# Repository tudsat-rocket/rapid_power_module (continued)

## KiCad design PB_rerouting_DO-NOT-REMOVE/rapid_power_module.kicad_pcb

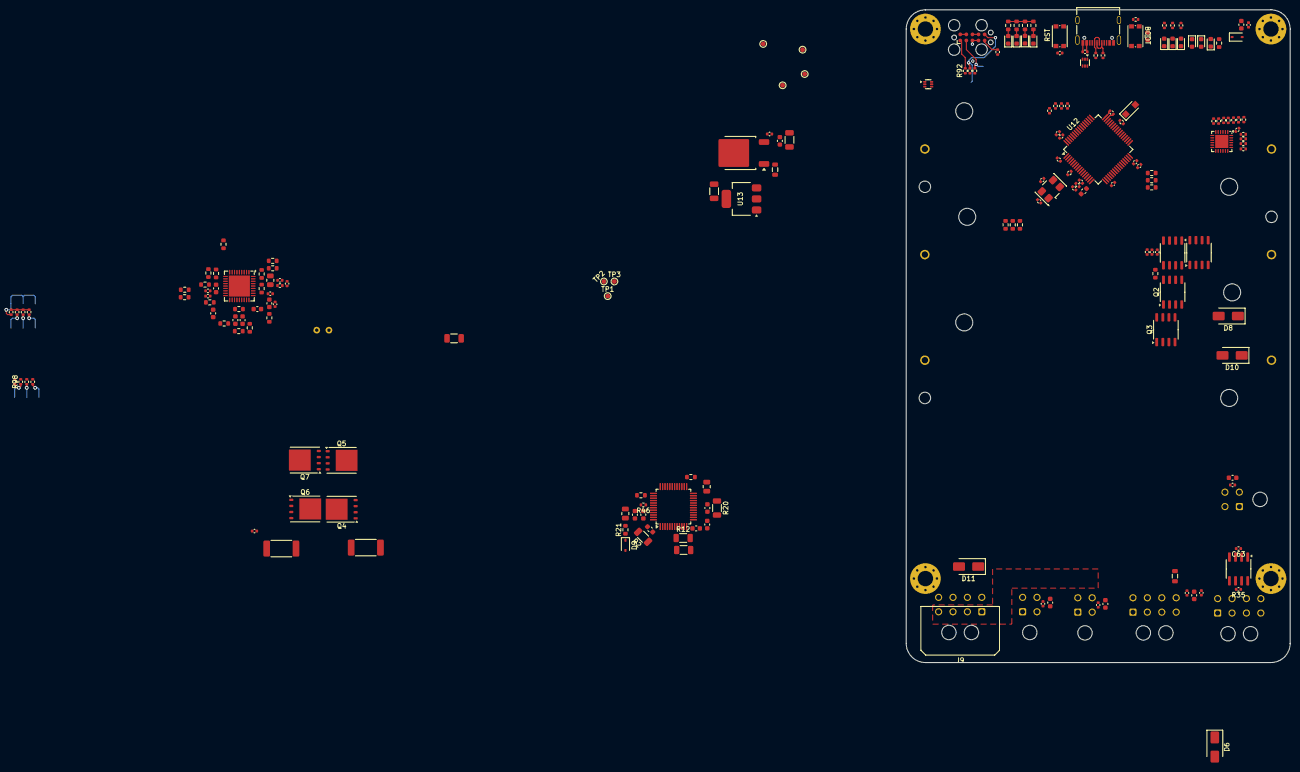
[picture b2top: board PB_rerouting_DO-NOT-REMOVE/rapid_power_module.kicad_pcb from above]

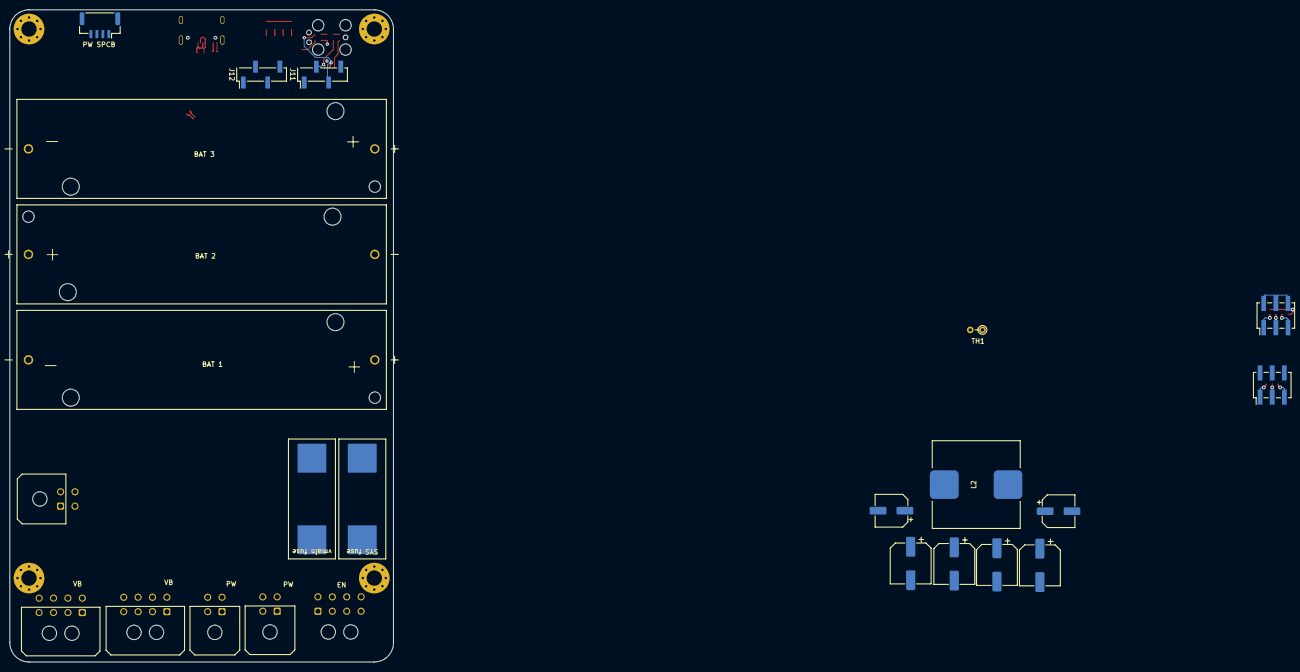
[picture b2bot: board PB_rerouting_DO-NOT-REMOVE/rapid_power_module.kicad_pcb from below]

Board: 4 copper layers, 80.0 x 136.0 mm, 210 parts (23 on the bottom side), 131 nets.

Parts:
BT1, BT2, BT3: Battery_Cell; BAT_1043
C1, C3, C37, C38, C44, C45, C60, C63, C68, C69, C70, C71, C72, C79, C81: 100n; C_0402_1005Metric
C2, C4, C5, C6: 82u; CP_Elec_8x6.9
C7, C8: 10u; CP_Elec_6.3x5.9
C9, C10, C20, C65, C74, C75: 1u; C_0402_1005Metric
C11: 1u; R_0402_1005Metric
C12, C13: 100n; R_0402_1005Metric
C14, C15, C16, C17: 220n; C_0603_1608Metric
C18, C39, C43, C47, C48, C58: 470n; C_0603_1608Metric
C19: 1u; C_0805_2012Metric
C21: 2u2; C_0805_2012Metric
C23: 3u3; C_0402_1005Metric
C24: 100p; C_0603_1608Metric
C46, C49: 47n; C_0603_1608Metric
C61: 10u; C_1206_3216Metric
C62: 0.47uF; C_1206_3216Metric
C67: 4u7; C_0402_1005Metric
C73, C76, C83, C85, C87, C89, C91: 10n; C_0402_1005Metric
C77, C78: 10p; C_0402_1005Metric
C80: 22u; C_1206_3216Metric
C82, C84, C86, C88, C90: 10u; C_0603_1608Metric
D4, D9: D_SOD-323
D5, D7, D16, D19, D21, D23: green; LED_0603_1608Metric
D6, D8, D10, D11: D_SMA
D17, D22: red; LED_0603_1608Metric
D18, D20: yellow; LED_0603_1608Metric
D24: Vz = 3.6V; Nexperia_CFP3_SOD-123W
F1: 5A; Fuseholder_Cylinder-5x20mm_Wuerth_696103101002-SMD_Horizont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
F3: 20A; Fuseholder_Cylinder-5x20mm_Wuerth_696103101002-SMD_Horizont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
FB1: 120R; L_0603_1608Metric
FB2, FB3: 120R; L_0805_2012Metric
H1, H2, H3, H4: MountingHole_Pad; MountingHole_3.2mm_M3_Pad_Via
J1, J3, J9: Conn_02x04_Top_Bottom; Molex_Micro-Fit_3.0_43045-0800_2x04_P3.00mm_Horizontal
J2, J4: Conn_02x03_Odd_Even; PinHeader_2x03_P2.54mm_Vertical_SMD
J6, J7, J8: Molex MicroFit 2x2; Molex_Micro-Fit_3.0_43045-0400_2x02_P3.00mm_Horizontal
J10: JST-GH 4Pin; JST_GH_SM04B-GHS-TB_1x04-1MP_P1.25mm_Horizontal
J11, J12: SWD Header; PinHeader_1x04_P2.54mm_Vertical_SMD_Pin1Left
J16: USB_C_Receptacle_USB2.0; USB_C_Receptacle_Palconn_UTC16-G
J17: TC2050; Tag-Connect_TC2050-IDC-FP_2x05_P1.27mm_Vertical
L2: 5u6; Wuerth 7443557560
Q1, Q2, Q3, Q12: AOSP21321; SO-8_3.9x4.9mm_P1.27mm
Q4: HiDRV1; TDSON-8-1
Q5: LoDRV1; TDSON-8-1
Q6: HiDRV2; TDSON-8-1
Q7: LoDRV2; TDSON-8-1
R1: 2.4; R_0402_1005Metric
R2, R11, R12, R20: 20; R_1206_3216Metric
R3: 15k; R_0603_1608Metric
R4, R13, R46, R95: 10k; R_0402_1005Metric
R5, R9, R26, R74, R89, R90: 1k; R_0402_1005Metric
R6, R7, R10, R18, R19, R96: 5k1; R_0402_1005Metric
R8, R30: 49k9; R_0603_1608Metric
R14, R15, R16, R17, R34: 1k; R_0603_1608Metric
R21: 100; R_0603_1608Metric
R22: 10R; R_0603_1608Metric
R23, R32: 4k7; R_0603_1608Metric
R24: 100k; R_0603_1608Metric
R25, R94, R97: 20k; R_0402_1005Metric
R27: 50k; R_0402_1005Metric
R28: 20k; R_0603_1608Metric
R29: 680; R_0603_1608Metric
R31: 50k; R_0603_1608Metric
R33: 300k; R_0603_1608Metric
R35: 120; C_0402_1005Metric
R36: 200k; R_0603_1608Metric
R37, R41, R79, R80: 10; R_0603_1608Metric
R38, R65: 5m; R_2512_6332Metric_Pad1.40x3.35mm_HandSolder
R39: 4.7k; R_0603_1608Metric
R40, R42, R64, R69, R70, R72, R91: 10k; R_0603_1608Metric
R43: 68k; R_0603_1608Metric
R44: 1000k; R_0805_2012Metric
R45: 4k7; R_0402_1005Metric
R66, R67: 4.7k; R_0402_1005Metric
R73, R75, R77, R78: 22R; R_0402_1005Metric
R76: 100k; R_0402_1005Metric
R82: 22k; R_0603_1608Metric
R83: 49k9; R_0402_1005Metric
R86, R87, R88, R92: 22; R_0402_1005Metric
R98: 15k; R_0402_1005Metric
SW1, SW2: KMR721NGLFS; SW_Push_1P1T_NO_CK_KMR2
TH1: Thermistor_NTC; R_Axial_DIN0204_L3.6mm_D1.6mm_P2.54mm_Vertical
TP1: BuckBoostOut; TestPoint_Pad_D1.0mm
TP2: TP_CAN_TX; TestPoint_Pad_D1.0mm
TP3: TP_CAN_RX; TestPoint_Pad_D1.0mm
TP4: TP_USB_D+; TestPoint_Pad_D1.0mm
TP5: TP_USB_D-; TestPoint_Pad_D1.0mm
TP6: TP_USB_CC2; TestPoint_Pad_D1.0mm
TP7: TP_USB_CC1; TestPoint_Pad_D1.0mm
U1: BQ25756RRVR; Texas_RHH0036C_VQFN-36-1EP_6x6mm_P0.5mm_EP4.4x4.4mm
U2: CYPD3177-24LQ; QFN-24-1EP_4x4mm_P0.5mm_EP2.75x2.75mm
U3: BQ76952PFBR; TQFP-48_7x7mm_P0.5mm
U10: L7805; TO-252-2
U11: MCP2562-E-SN; SOIC-8_3.9x4.9mm_P1.27mm
U12: STM32F105RCTx; LQFP-64_10x10mm_P0.5mm
U13: AZ1117I-3.3; SOT-223-3_TabPin2
U14, U15: TPD4E1U06; SOT-563
Y3: 8MHz 12pF; Crystal_SMD_5032-4Pin_5.0x3.2mm

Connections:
3.3V PD: C11.1, C12.1, C13.1, R6.1, R10.1, R18.1, U2.23 (VDDD)
+3V3: C67.1, C68.1, C69.1, C70.1, C71.1, C72.1, C75.1, C76.1, C80.2, FB1.1, J11.1, J12.1, J17.7, J17.8, R14.1, R15.1, R16.1, R17.1, R26.1, R34.1, R39.1, R40.1, R42.1, R64.1, R66.2, R67.2, R69.1, R70.1, R72.1, R89.1, R90.1, U11.5 (Vio), U12.1 (VBAT), U12.19 (VDD), U12.32 (VDD), U12.48 (VDD), U12.64 (VDD), U13.2 (VO), U15.5 (IO4)
+3VA3: C73.1, C74.1, FB1.2, U12.13 (VDDA)
+5V: C60.1, C61.2, C63.2, J17.9, J17.10, U10.3 (OUT), U11.3 (VDD), U13.3 (VI), U15.6 (V_{cc})
+VSW: C84.1, C85.1, C86.1, C87.1, C88.1, C89.1, D11.2 (A), J6.3, J6.4, J7.3, J7.4, J8.3, J8.4, J9.1, J9.2, J9.3, J9.4
/D0+: J16.A6 (D+), J16.B6 (D+), R75.2, U14.5 (IO4)
/D0-: J16.A7 (D-), J16.B7 (D-), R73.1, U14.4 (IO3)
/J1-SWCLK: J11.3, J17.6, R88.1, U15.4 (IO3)
/J1-SWDIO: J11.2, J17.2, R86.2, U15.1 (IO1)
/J1-SWO: J17.5, R87.2, U15.2 (IO2)
/VBUS: C9.1, C23.2, J16.A4 (VBUS), J16.A9 (VBUS), J16.B4 (VBUS), J16.B9 (VBUS), Q2.5 (D), Q2.6 (D), Q2.7 (D), Q2.8 (D), Q12.5 (D), Q12.6 (D), Q12.7 (D), Q12.8 (D), R4.1, R8.1, R45.2, U2.18 (VBUS_IN), U14.6 (V_{cc})
/VCC_BQ76952: C18.2, C19.2, C24.2, R21.2, U3.47 (BAT)
/V_in_post_sense: C4.1, C7.1, Q4.5 (D), R65.2, R79.1
ACN: C38.1, C39.1, R79.2, U1.29 (ACN)
ACOV: R33.2, R43.1, U1.35 (ACOV)
ACP: C37.2, C39.2, R80.2, U1.30 (ACP)
ACUV: R33.1, R44.2, U1.34 (ACUV)
BAL_ALERT: R23.1, U3.25 (ALERT), U12.24 (PC4)
BOOT: R76.2, SW1.1 (A), U12.60 (BOOT0), U14.1 (IO1)
BTST1: C49.2, U1.26 (BTST1)
BTST2: C46.2, U1.20 (BTST2)
BuckBoostOut: C6.1, Q6.5 (D), R38.1, R41.2, TP1.1
CAN+: J1.7, J3.7, R35.1, U11.7 (CANH)
CAN-: J1.3, J3.3, R35.2, U11.6 (CANL)
CAN_2_H: J1.8, J3.8
CAN_2_L: J1.4, J3.4
CAN_RX: TP3.1, U11.4 (RXD), U12.61 (PB8)
CAN_TX: TP2.1, U11.1 (TXD), U12.62 (PB9)
CC1: J16.A5 (CC1), TP7.1, U2.15 (CC1)
CC2: J16.B5 (CC2), TP6.1, U2.14 (CC2)
CE: R91.2, U1.7 (CE), U12.40 (PC9)
CELL 0: C17.2, R20.2, U3.16 (VC0)
CELL 1: C15.2, C16.1, R12.2, U3.15 (VC1)
CELL 2: C14.2, C15.1, R11.2, U3.1 (VC15), U3.2 (VC14), U3.3 (VC13), U3.4 (VC12), U3.5 (VC11), U3.6 (VC10), U3.7 (VC9), U3.8 (VC8), U3.9 (VC7), U3.10 (VC6), U3.11 (VC5), U3.12 (VC4), U3.13 (VC3), U3.14 (VC2)
CELL 3: C14.1, R2.2, U3.48 (VC16)
CHRG_IND_LED_1: D5.1 (K), U12.54 (PD2)
CHRG_IND_LED_2: D7.1 (K), U12.55 (PB3)
CHRG_IND_LED_3: D16.1 (K), U12.56 (PB4)
CHRG_IND_LED_4: D23.1 (K), U12.57 (PB5)
FAULT: R40.2, U2.9 (FAULT), U12.27 (PB1)
FLIP: R39.2, U2.10 (FLIP), U12.26 (PB0)
GND: BT3.N (-), C1.2, C2.2, C3.2, C4.2, C5.2, C6.2, C7.2, C8.2, C11.2, C12.2, C13.2, C16.2, C17.1, C19.1, C20.2, C21.1, C23.1, C24.1, C37.1, C38.2, C44.2, C45.1, C47.2, C48.2, C58.1, C60.2, C61.1, C62.2, C63.1, C65.2, C67.2, C68.2, C69.2, C70.2, C71.2, C72.2, C73.2, C74.2, C75.2, C76.2, C77.2, C78.2, C79.1, C80.1, C81.2, C82.2, C83.2, C84.2, C85.2, C86.2, C87.2, C88.2, C89.2, C90.2, C91.2, D20.1 (K), D21.1 (K), D24.2 (A), H1.1, H2.1, H3.1, H4.1, J1.1, J1.2, J3.1, J3.2, J6.1, J6.2, J7.1, J7.2, J8.1, J8.2, J10.3, J10.4, J11.4, J12.4, J16.A1 (GND), J16.A12 (GND), J16.B1 (GND), J16.B12 (GND), J16.S1 (SHIELD), J17.3, J17.4, Q5.1 (S), Q5.2 (S), Q5.3 (S), Q7.1 (S), Q7.2 (S), Q7.3 (S), R7.2, R13.2, R19.2, R20.1, R23.2, R24.2, R25.2, R27.2, R29.2, R31.2, R43.2, R76.1, R83.2, R91.1, R94.2, R95.2, R96.2, R97.2, R98.2, SW2.1 (A), TH1.2, U1.17 (PGND), U1.22 (PGND), U1.37 (EPAD), U2.6 (ISNK_FINE), U2.19 (GND), U2.22 (GND), U2.25 (GND), U3.17 (VSS), U3.18 (SRP), U3.20 (SRN), U3.36 (REGIN), U3.37 (BREG), U3.41 (LD), U10.2 (GND), U11.2 (VSS), U11.8 (STBY), U12.12 (VSSA), U12.18 (VSS), U12.31 (VSS), U12.47 (VSS), U12.63 (VSS), U13.1 (GND), U14.3 (GND), U15.3 (GND), Y3.2, Y3.4
GPIO_1: R42.2, U2.8 (GPIO_1), U12.28 (PB2)
HIDRV1: Q4.4 (G), U1.27 (HIDRV1)
HIDRV2: Q6.4 (G), U1.19 (HIDRV2)
HSE_IN: C78.1, U12.5 (PD0), Y3.3
HSE_OUT: R74.1, U12.6 (PD1)
I2C_SCL: R67.1, R78.1, U1.1 (SCL), U2.13 (HPI_SCL), U3.26 (SCL), U12.58 (PB6)
I2C_SDA: R66.1, R77.1, U1.2 (SDA), U2.12 (HPI_SDA), U3.27 (SDA), U12.59 (PB7)
INT: R72.2, U1.3 (INT), U12.51 (PC10)
ISNK_COARSE: R10.2, R13.1, U2.5 (ISNK_COARSE)
LODRV1: Q5.4 (G), U1.25 (LODRV1)
LODRV2: Q7.4 (G), U1.21 (LODRV2)
NRST: C79.2, R92.1, SW2.2 (B), U12.7 (NRST), U14.2 (IO2)
unnamed: BT1.N (-), BT2.P (+), R11.1
unnamed: BT2.N (-), BT3.P (+), R12.1
unnamed: C1.1, R1.1
unnamed: C77.1, R74.2, Y3.1
unnamed: D4.1 (K), J10.1, J10.2
unnamed: D5.2 (A), R14.2
unnamed: D7.2 (A), R15.2
unnamed: D9.1 (K), R21.1
unnamed: D11.1 (K), F1.1
unnamed: D16.2 (A), R16.2
unnamed: D17.2 (A), R26.2
unnamed: D18.2 (A), R89.2
unnamed: D19.2 (A), R90.2
unnamed: D22.2 (A), R69.2
unnamed: D23.2 (A), R17.2
unnamed: F1.2, FB2.2
unnamed: J2.1, R25.1
unnamed: J2.2, J2.4, J2.6, R94.1, U1.10 (ILIM_HIZ)
unnamed: J2.3, R95.1
unnamed: J2.5, R96.1
unnamed: J4.1, R27.1
unnamed: J4.2, J4.4, J4.6, R83.1, U1.9 (ICHG)
unnamed: J4.3, R97.1
unnamed: J4.5, R98.1
unnamed: F3.1, J9.5, J9.6, J9.7, J9.8
unnamed: J12.2, R78.2
unnamed: J12.3, R77.2
unnamed: J17.1, R92.2
unnamed: Q1.5 (D), Q1.6 (D), Q1.7 (D), Q1.8 (D), Q12.1 (S), Q12.2 (S), Q12.3 (S)
unnamed: C9.2, C10.2, Q1.4 (G), Q12.4 (G), R4.2, R5.1
unnamed: Q2.4 (G), Q3.4 (G), R8.2, R9.1
unnamed: Q2.1 (S), Q2.2 (S), Q2.3 (S), Q3.5 (D), Q3.6 (D), Q3.7 (D), Q3.8 (D)
unnamed: R3.2, R28.1
unnamed: R29.1, R82.2
unnamed: R30.2, R36.1
unnamed: R34.2, SW1.2 (B)
unnamed: C48.1, R22.2, U1.23 (DRV_SUP)
unnamed: R28.2, R30.1, U1.12 (FB)
unnamed: R3.1, U1.11 (FBG)
unnamed: R31.1, U1.36 (FSW_SYNC)
unnamed: R32.1, R82.1, TH1.1, U1.8 (TS)
unnamed: C20.1, U2.24 (VCCD)
unnamed: C18.1, U3.46 (CP1)
unnamed: R24.1, U3.38 (FUSE)
unnamed: R46.1, U3.42 (PACK)
unnamed: C21.2, U3.24 (REG18)
unnamed: C58.2, FB3.1, U10.1 (IN)
PACK+: BT1.P (+), C3.1, C5.1, C8.1, C90.1, C91.1, D4.2 (A), D9.2 (A), F3.2, FB3.2, R2.1, R36.2, R37.2, R38.2, R46.2
PG: D22.1 (K), U1.6 (PG), U12.36 (PB15)
REGN: C47.1, R22.1, R32.2, U1.24 (REGN)
RST_SHUT: U3.33 (RST_SHUT), U12.2 (PC13)
SAFE_PWR_EN: R9.2, U2.4 (SAFE_PWR_EN)
SAFE_PWR_OUT: D10.2 (A), Q3.1 (S), Q3.2 (S), Q3.3 (S)
SRN: C43.2, C45.2, R37.1, U1.13 (SRN)
SRP: C43.1, C44.1, R41.1, U1.14 (SRP)
STAT1: D20.2 (A), R64.2, U1.4 (STAT1), U12.38 (PC7)
STAT2: D21.2 (A), R70.2, U1.5 (STAT2), U12.37 (PC6)
STAT_LED0: D17.1 (K), U12.33 (PB12)
STAT_LED1: D18.1 (K), U12.34 (PB13)
STAT_LED2: D19.1 (K), U12.35 (PB14)
SW1: C49.1, L2.1, Q4.1 (S), Q4.2 (S), Q4.3 (S), Q5.5 (D), U1.28 (SW1)
SW2: C46.1, L2.2, Q6.1 (S), Q6.2 (S), Q6.3 (S), Q7.5 (D), U1.18 (SW2)
SWCLK: R88.2, U12.49 (PA14)
SWDIO: R86.1, U12.46 (PA13)
SWO: R87.1, U12.50 (PA15)
TS2: U3.22 (TS2), U12.17 (PA3)
USB_D+: R75.1, TP4.1, U12.45 (PA12)
USB_D-: R73.2, TP5.1, U12.44 (PA11)
USB_FS_VBUS: D24.1 (K), R45.1, U12.42 (PA9)
USB_PD_INTERRUPT: U2.7 (~HPI_INT), U12.21 (PA5)
USB_PD_OUT: C10.1, D8.2 (A), Q1.1 (S), Q1.2 (S), Q1.3 (S), U2.11 (VDC_OUT)
VBUS_FET_EN: R5.2, U2.3 (VBUS_FET_EN)
VBUS_MAX: R6.2, R7.1, U2.2 (VBUS_MAX)
VBUS_MIN: R18.2, R19.1, U2.1 (VBUS_MIN)
V_in: C2.1, C62.1, C65.1, D6.1 (K), D8.1 (K), D10.1 (K), R1.2, R44.1, R65.1, R80.1, U1.32 (VAC), U1.33 (VAC)
charging_voltage: D6.2 (A), J1.5, J3.5
main_voltage: C81.1, C82.1, C83.1, FB2.1, J1.6, J3.6

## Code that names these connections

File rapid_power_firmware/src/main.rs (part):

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    let p = embassy_stm32::init(config);
    defmt::info!("main.rs: Embassy is up.");

    // ---- BQ25756 CE pin (PC9) ----
    // Drive LOW to allow charging (CE is active-low on this design)
    let bq_ce = Output::new(p.PC9, Level::Low, Speed::VeryHigh);
    // keep it in scope (or move into a StaticCell) so it stays driven for the lifetime
    core::mem::forget(bq_ce);

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    let usb_driver: OtgDriver<'static, USB_OTG_FS> = OtgDriver::new_fs(
        p.USB_OTG_FS,
        Irqs,
        p.PA12,
        p.PA11,
        EP_MEMORY.init([0; 4096]),
        otg_cfg,
    );
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    // I2C bus + shared device handles
    let mut i2c_cfg = I2cConfig::default();
    i2c_cfg.frequency = Hertz(100_000);
    let raw_i2c = I2c::new(p.I2C1, p.PB6, p.PB7, Irqs, p.DMA1_CH6, p.DMA1_CH7, i2c_cfg);
    let bus_mutex: &'static I2cBusMutex = I2C_BUS.init(Mutex::new(raw_i2c));

    // BQ25756
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        let bq25756 = bq25756::Bq25756::new(i2c_dev);
        let bq25756_mutex = BQ25756_DRV.init(Mutex::new(bq25756));

        let bq_int   = ExtiInput::new(p.PC10, p.EXTI10, Pull::Up);
        let bq_stat1 = ExtiInput::new(p.PC7,  p.EXTI7,  Pull::Up);
        let bq_stat2 = ExtiInput::new(p.PC6,  p.EXTI6,  Pull::Up);
        let bq_pg    = ExtiInput::new(p.PB15, p.EXTI15, Pull::Up);

        defmt::info!("main.rs: Spawning BQ25756 tasks");
        spawner
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    // --- BQ76952 FIRST ---
    #[cfg(feature = "bq76952")]
    {
        let ts2 = Flex::new(p.PA3);
        let i2c_dev: I2cDev<'static> = I2cDevice::new(bus_mutex);
        let bq = bq76952::Bq76952::new(i2c_dev, 0x08, 5);
        let bq_mutex = BQ76952_DRV.init(Mutex::new(bq));
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                let cypd_mutex = CYPD_DRV.init(Mutex::new(cypd_tmp));

                // IRQ pin
                let hpi_int = ExtiInput::new(p.PA5, p.EXTI5, Pull::Up);

                // Spawn tasks ONLY if probe passed
                spawner.spawn(cypd3177::device::cypd_monitor_task(cypd_mutex)).unwrap();
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    // CAN
    #[cfg(feature = "can")]
    {
        let can = can::init(p.CAN1, p.PB8, p.PB9, Irqs);
        spawner.spawn(can::run(can)).unwrap();
    }
} // <-- CLOSES main
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
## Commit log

2024-11-18 add readme
2024-11-18 fix image path
2025-03-22 Added 2 ICs to library, added these ICs to the schaltplan. Added Readme Notes
2025-04-23 Weitere Änderungen, aber noch nicht fertig
2025-04-28 Zwischenstand
2025-04-29 Cell Balancer Reading Circuit cleaned up
2025-04-29 Cleaned up
2025-05-05 Added MCU and connected relevant Pins
2025-05-10 clean up
2025-05-10 more cleanup
2025-05-11 project cleanup and renaming
2025-05-11 update parts
2025-05-11 Added Falstadt simulator file, incomplete
2025-05-12 added some connectors, components and todos
2025-05-12 excel
2025-05-19 Added BG25756 and exchanged it against BG25750 Changed the circuitry accordingly ToDo: Change values of resistors and caps to match final voltage and capacity
2025-05-20 Werte geupdatet
2025-05-20 finalized excel sheet -> picture & values in scematic not adjusted jet, added some footprints and parts
2025-05-21 Added comments
2025-05-23 changed values in the Buck Boost Section according to the excel sheet
2025-05-26 Added first design for the usb PD funtionality and added comments
2025-05-26 Kommentare
2025-05-31 added drawio overview in docs
2025-06-07 Added TODOs in Schematic
2025-06-08 added diode logic
2025-06-13 added charge indicator LEDs
2025-06-13 fixed vbus sense for usb pd
2025-06-13 balancer circuit with new chip
2025-06-13 changed GND in the PACK
2025-06-15 comments and a bit of cleanup
2025-06-23 changed back to bq76952
2025-06-23 saving work
2025-06-23 changed GND to VSS
2025-06-23 changed buck boost values according to the excel tool
2025-06-23 work on the Balancer
2025-06-23 added balancer datasheet
2025-06-27 added some footprints
2025-07-04 some comments and checking
2025-07-04 added most footprints
2025-07-07 Removed BJT as it is not required when not using REG1 and REG2
2025-07-21 Added Testpoints and some LCSC numbers
2025-07-28 Routing for 4 pin connectors
2025-08-01 rough component placement
2025-08-01 some placement changes
2025-08-02 more routing work
2025-08-02 Added Footprints for MOSFETs
2025-08-02 Further Routing work and fixed the Q Pins
2025-08-03 Placed the NMOS near Inductor, moved STM out of the way and fixed the Battery Pins
2025-08-03 Fixed wuerth cap footprints and values
2025-08-03 Added footprints and LCSC
2025-08-04 Added Diode and new connector type
2025-08-04 fix diode and more routing work
2025-08-04 Added Pin connections from USB PD to STM, removed non essential resistors
2025-08-06 more routing
2025-08-06 Fixed Balancer Pins so that LDO is not used and LDO input is grounded
2025-08-06 Annotated change
2025-08-07 improve area shapes
2025-08-07 check DRC and fix issues
2025-08-11 gnd changes in scematic and routing, tbc
2025-08-11 some changes in the scematic
2025-08-11 assimilated ground connections
2025-08-12 croschecking scematic, some changes there and new routing approach
2025-08-14 scematic adaptations and routing
2025-08-15 Stop tracking embedded repo rapid_power_fw, added LD schemtaic
2025-08-15 Ignore rapid_power_fw
2025-08-15 some scematic changes and routing
2025-08-16 Added new Resistor for LD so that it can detect load and charger
2025-08-17 Continue with routing, esp. signal traces for mcu
2025-08-17 Length matching, some cleanup, additional via placement
2025-08-17 finish routing and silkscreen improvements
2025-08-17 Finishing touches (Zone optimizations to reduce antenna effect, wider battery connection zones)
2025-08-17 Replace wrong battery manager footprint
2025-08-21 Fix: remove embedded repo and commit project updates
2025-08-29 Add basic running embassy loop
2025-09-01 Update dependencies and add CYPD3177 driver
    - Updated `defmt`, `defmt-rtt`, and `panic-probe` dependencies to version 1.0.1, 1.0.0, and 1.0.0 respectively.
    - Upgraded `embassy-stm32`, `embassy-executor`, `embassy-time`, `embassy-embedded-hal`, and `embassy-sync` to their latest versions.
    - Got it to actually run.
    - Introduced a new module `cypd3177.rs` for the CYPD3177 USB-PD async driver, implementing HPI over I²C.
    - Refactored `main.rs` to integrate the new CYPD3177 driver, including tasks for USB communication and monitoring the CYPD3177 status.
    - Added support for handling USB CDC communication and periodic monitoring of the CYPD3177 device status.
2025-09-02 Add async driver for BQ76952 battery monitor
    - Implemented the Bq76952 struct with methods for initialization, reading measurements, and configuring settings.
    - Added support for direct commands and subcommands as per the Technical Reference Manual (TRM).
    - Created register addresses and bit masks in a separate `regs` module.
    - Defined necessary types, enums, and error handling in the `types` module.
    - Included methods for voltage, current, temperature readings, and protection settings.
    - Added functionality for I2C address configuration and data memory writing.
2025-09-04 Enhance BQ76952 driver with TS2 control and wake functionality; add new features for GPIO handling in main application
2025-09-04 Add BQ25756 driver with async support and integrate into main application
2025-09-08 Added initial working driver for v3 of power module
2025-09-09 temp commit
2025-09-24 Cleaned up BQ25756, cleaned up repo
2025-09-24 Refactor BQ25756 configuration and enhance driver functionality
    - Updated default features in Cargo.toml
    - Added known errors section in README.md
    - Introduced new helper functions and improved existing methods in device.rs for better handling of DPM limits
    - Enhanced logging for charge and input current limits
    - Adjusted logging period and maximum charge/input current in config.rs
2025-09-27 Comments and Thermistor Code
2025-09-27 BQ25756: Fixed bit shift handling in ICHG and Voltage DPM
2025-09-27 Fixed max battery voltage
2025-10-13 fix broken trace
2025-11-04 Added new charger architecture of rapid_power_module.kicad_sch
2025-11-04 fixed open-message
2025-11-04 added todos
2025-11-05 added hierarchical pins for submodules
2025-11-09 added second i2c bus; cleaned up sub-schematic-structure
2025-11-10 Cleaned up, added some Balancer designs
2025-11-10 Cleaned up, added some Balancer designs, cleaned up folder
2025-11-22 cleaned up hierarchical structure; changed connectors
2025-11-30 added SA balancer design (WiP)
2025-12-03 added balancer thermistor info; changed MCU pinout to support CAN bootloading
2025-12-07 Changed Balancer layout to support OVP, UVP and UVP-circumvention; added UVP-circumvention arming connector
2025-12-14 added explanations for balancer schematic and some component values
2025-12-15 changed balancer layout according to new requirements (i.e. removed OVP/UVP, OTP/UTP, OCP/UCP); reduced arming connectors to only one
2025-12-21 added info text
2025-12-22 finalized new balancer layout (removed R_SNS and implemented the resulting consequences); removed charger shipping mode
2026-01-13 changed arming_pin2battery connection
2026-01-28 implemented changes according to errors found in the schematic design review (wip)
2026-02-02 added missing footprints and validated all lcsc numbers; started pcb-layouting
2026-03-09 started routing Please enter the commit message for your changes. Lines starting
2026-03-16 still working on routing
2026-03-22 completed signal routing
2026-04-11 almost finished routing
2026-04-19 finished pcb routing. needs feedback
2026-04-21 implemented improvements based on feedback; Voltage/Current sensing still missing
2026-04-21 added 3D model for 20A fuse holder
2026-04-23 adding voltage and current sensing capabilities. WIP
2026-04-27 calculated sensing-resistor values
2026-04-29 added current sensing circuit
2026-04-30 finished adding sensing-capabilities (incl. routing)
2026-05-19 preparing for order
2026-05-21 added test points
2026-05-21 added thermal reliefs
2026-05-22 adjusted a few label positions in pcb
2026-06-14 fix silkscreen issues and start implementing small layout improvements, cleanup repo
2026-06-14 remove backups from git
2026-06-17 current state, shrinked board, some adaptions still neccesarry
2026-06-17 removed lock
2026-06-26 finished routing adaptions
2026-06-26 edited do not place
2026-06-28 last changes (components) for ordering
2026-06-29 order version
